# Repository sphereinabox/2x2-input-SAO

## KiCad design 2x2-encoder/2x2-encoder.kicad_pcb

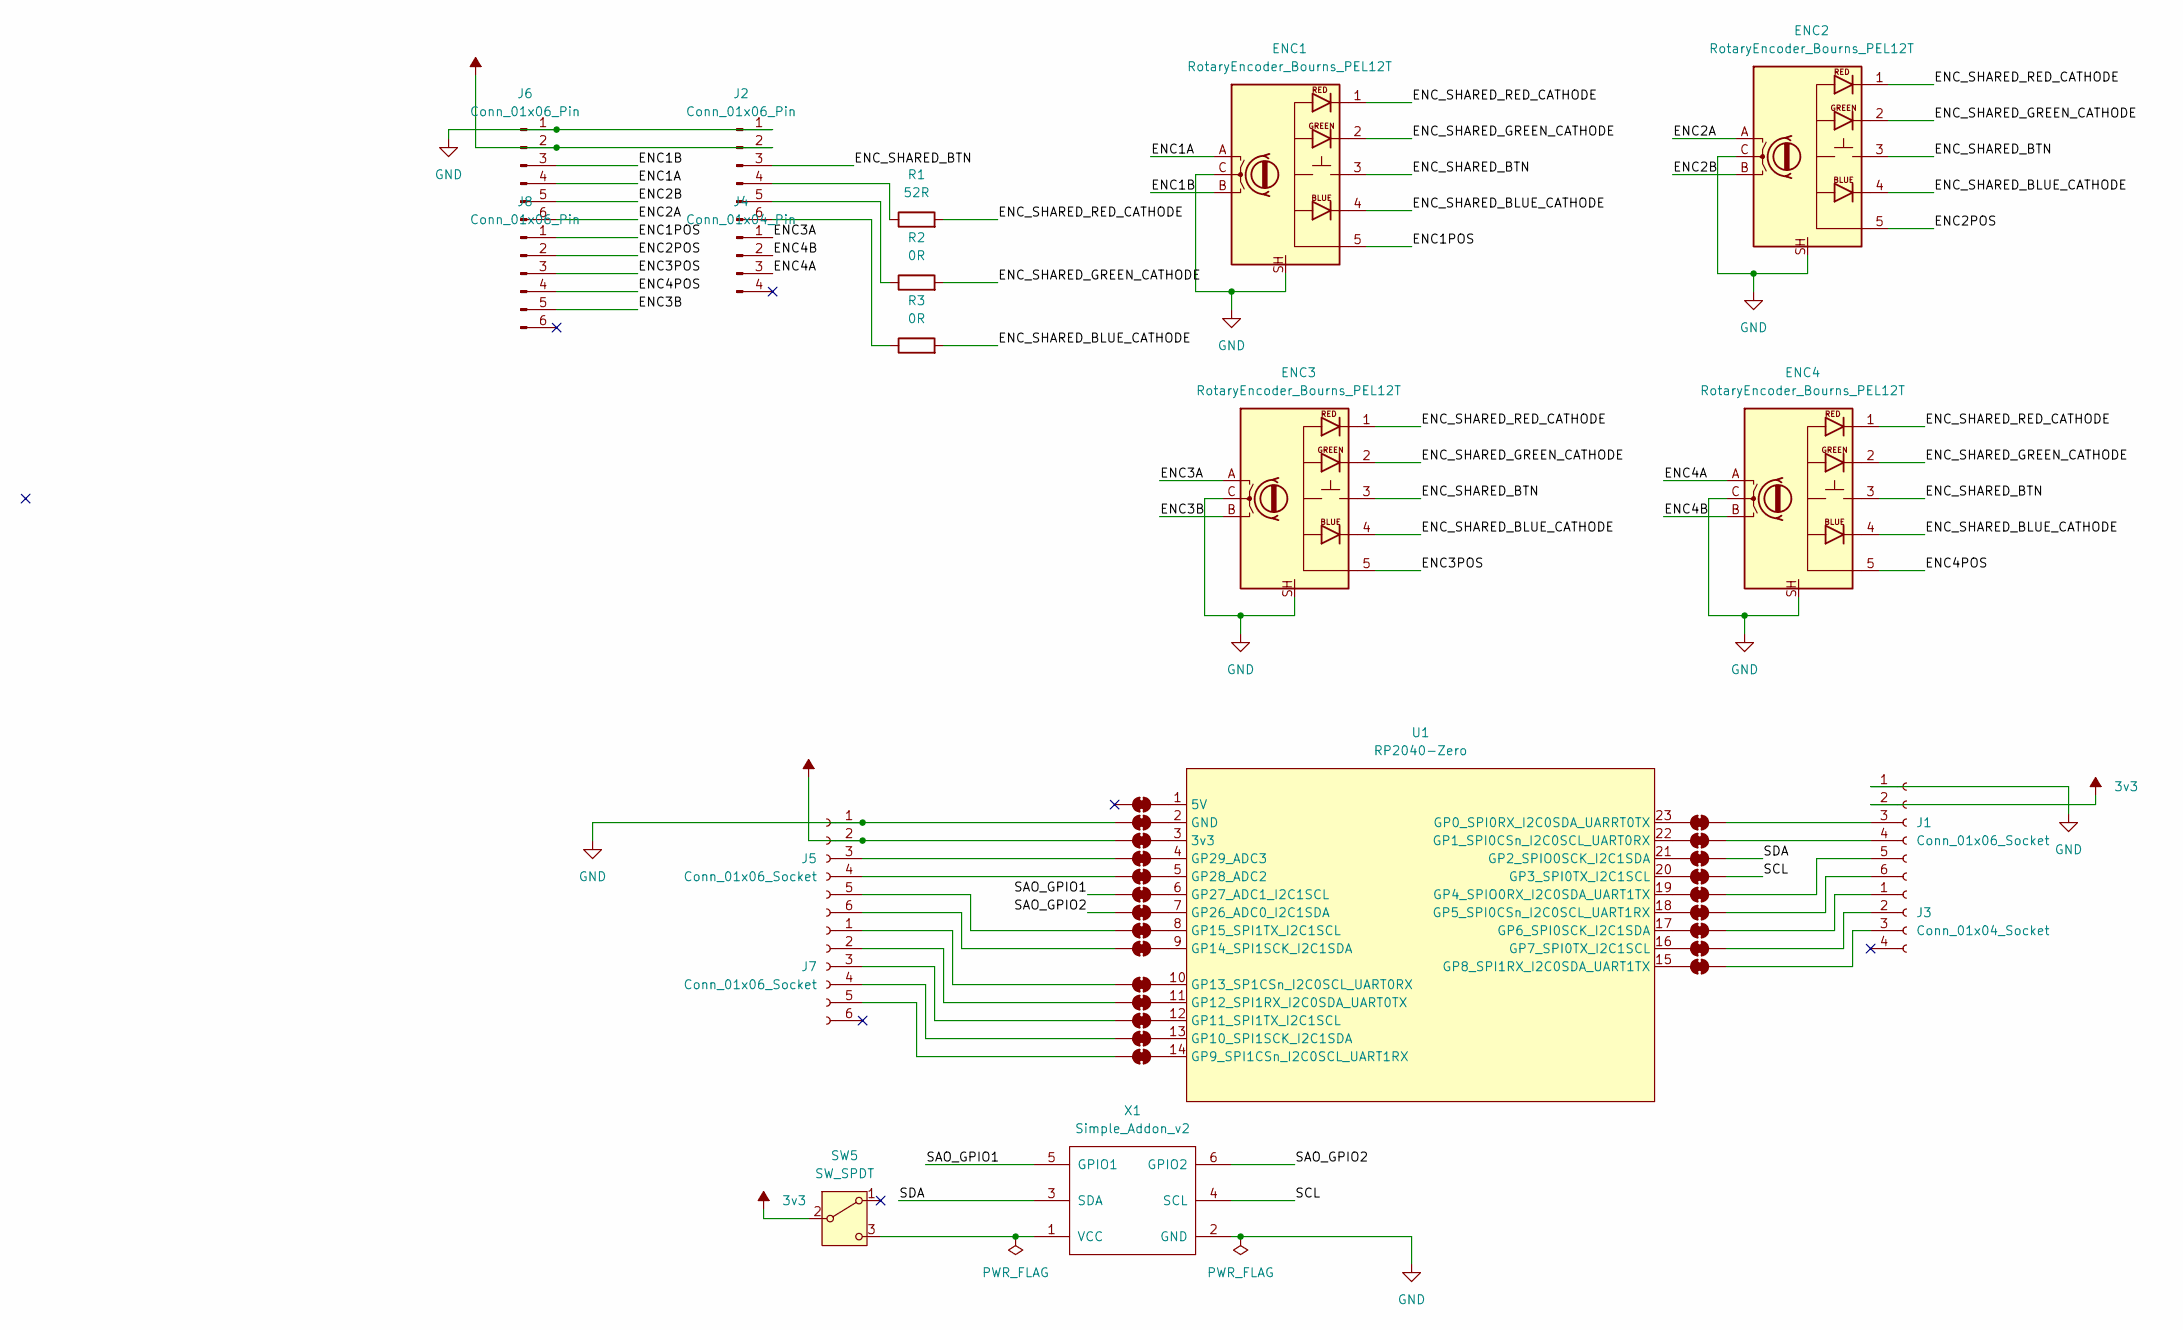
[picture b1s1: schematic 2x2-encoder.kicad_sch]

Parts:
ENC1, ENC2, ENC3, ENC4: RotaryEncoder_Bourns_PEL12T; RotaryEncoder_Bourns_Vertical_PEL12T-4x25S-Sxxxx
J1, J5, J7: Conn_01x06_Socket; PinSocket_1x06_P2.54mm_Vertical
J2, J6, J8: Conn_01x06_Pin; PinHeader_1x06_P2.54mm_Vertical
J3: Conn_01x04_Socket; PinSocket_1x04_P2.54mm_Vertical
J4: Conn_01x04_Pin; PinHeader_1x04_P2.54mm_Vertical
JP1, JP2, JP3, JP4, JP5, JP6, JP7, JP8, JP9, JP10, JP11, JP12, JP13, JP14, JP15, JP16, JP17, JP18, JP19, JP20, JP21, JP22, JP23: SolderJumper_2_Bridged; SolderJumper-2_P1.3mm_Bridged2Bar_Pad1.0x1.5mm
R1: 52R; R_0603_1608Metric_Pad0.98x0.95mm_HandSolder
R2, R3: 0R; R_0603_1608Metric_Pad0.98x0.95mm_HandSolder
SW5: SW_SPDT; SW_SPDT_PCM12
U1: RP2040-Zero; RP2040-Zero-PinHeaders
X1: Simple_Addon_v2; Simple_Addon_v2-SAO-2x3

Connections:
3v3: J1.2, J2.2, J5.2, J6.2, JP3.1 (A), SW5.2 (B)
/ENC1A: ENC1.A, J6.4
/ENC1B: ENC1.B, J6.3
/ENC1POS: ENC1.5, J8.1
/ENC2A: ENC2.A, J6.6
/ENC2B: ENC2.B, J6.5
/ENC2POS: ENC2.5, J8.2
/ENC3A: ENC3.A, J4.1
/ENC3B: ENC3.B, J8.5
/ENC3POS: ENC3.5, J8.3
/ENC4A: ENC4.A, J4.3
/ENC4B: ENC4.B, J4.2
/ENC4POS: ENC4.5, J8.4
/ENC_SHARED_BLUE_CATHODE: ENC1.4, ENC2.4, ENC3.4, ENC4.4, R3.2
/ENC_SHARED_BTN: ENC1.3, ENC2.3, ENC3.3, ENC4.3, J2.3
/ENC_SHARED_GREEN_CATHODE: ENC1.2, ENC2.2, ENC3.2, ENC4.2, R2.2
/ENC_SHARED_RED_CATHODE: ENC1.1, ENC2.1, ENC3.1, ENC4.1, R1.2
/SAO_GPIO1: JP6.1 (A), X1.5 (GPIO1)
/SAO_GPIO2: JP7.1 (A), X1.6 (GPIO2)
/SCL: JP18.2 (B), X1.4 (SCL)
/SDA: JP17.2 (B), X1.3 (SDA)
GND: ENC1.C, ENC1.SH, ENC2.C, ENC2.SH, ENC3.C, ENC3.SH, ENC4.C, ENC4.SH, J1.1, J2.1, J5.1, J6.1, JP2.1 (A), X1.2 (GND)
unnamed: J1.3, JP15.2 (B)
unnamed: J1.4, JP16.2 (B)
unnamed: J1.5, JP19.2 (B)
unnamed: J1.6, JP20.2 (B)
unnamed: J2.4, R1.1
unnamed: J2.5, R2.1
unnamed: J2.6, R3.1
unnamed: J3.1, JP21.2 (B)
unnamed: J3.2, JP22.2 (B)
unnamed: J3.3, JP23.2 (B)
unnamed: J5.3, JP4.1 (A)
unnamed: J5.4, JP5.1 (A)
unnamed: J5.5, JP8.1 (A)
unnamed: J5.6, JP9.1 (A)
unnamed: J7.1, JP10.1 (A)
unnamed: J7.2, JP11.1 (A)
unnamed: J7.3, JP12.1 (A)
unnamed: J7.4, JP13.1 (A)
unnamed: J7.5, JP14.1 (A)
unnamed: JP1.2 (B), U1.1 (5V)
unnamed: JP2.2 (B), U1.2 (GND)
unnamed: JP3.2 (B), U1.3 (3v3)
unnamed: JP4.2 (B), U1.4 (GP29_ADC3)
unnamed: JP5.2 (B), U1.5 (GP28_ADC2)
unnamed: JP6.2 (B), U1.6 (GP27_ADC1_I2C1SCL)
unnamed: JP7.2 (B), U1.7 (GP26_ADC0_I2C1SDA)
unnamed: JP8.2 (B), U1.8 (GP15_SPI1TX_I2C1SCL)
unnamed: JP9.2 (B), U1.9 (GP14_SPI1SCK_I2C1SDA)
unnamed: JP10.2 (B), U1.10 (GP13_SP1CSn_I2C0SCL_UART0RX)
unnamed: JP11.2 (B), U1.11 (GP12_SPI1RX_I2C0SDA_UART0TX)
unnamed: JP12.2 (B), U1.12 (GP11_SPI1TX_I2C1SCL)
unnamed: JP13.2 (B), U1.13 (GP10_SPI1SCK_I2C1SDA)
unnamed: JP14.2 (B), U1.14 (GP9_SPI1CSn_I2C0SCL_UART1RX)
unnamed: JP15.1 (A), U1.23 (GP0_SPI0RX_I2C0SDA_UARRT0TX)
unnamed: JP16.1 (A), U1.22 (GP1_SPI0CSn_I2C0SCL_UART0RX)
unnamed: JP17.1 (A), U1.21 (GP2_SPIO0SCK_I2C1SDA)
unnamed: JP18.1 (A), U1.20 (GP3_SPI0TX_I2C1SCL)
unnamed: JP19.1 (A), U1.19 (GP4_SPIO0RX_I2C0SDA_UART1TX)
unnamed: JP20.1 (A), U1.18 (GP5_SPI0CSn_I2C0SCL_UART1RX)
unnamed: JP21.1 (A), U1.17 (GP6_SPI0SCK_I2C1SDA)
unnamed: JP22.1 (A), U1.16 (GP7_SPI0TX_I2C1SCL)
unnamed: JP23.1 (A), U1.15 (GP8_SPI1RX_I2C0SDA_UART1TX)
unnamed: SW5.3 (C), X1.1 (VCC)

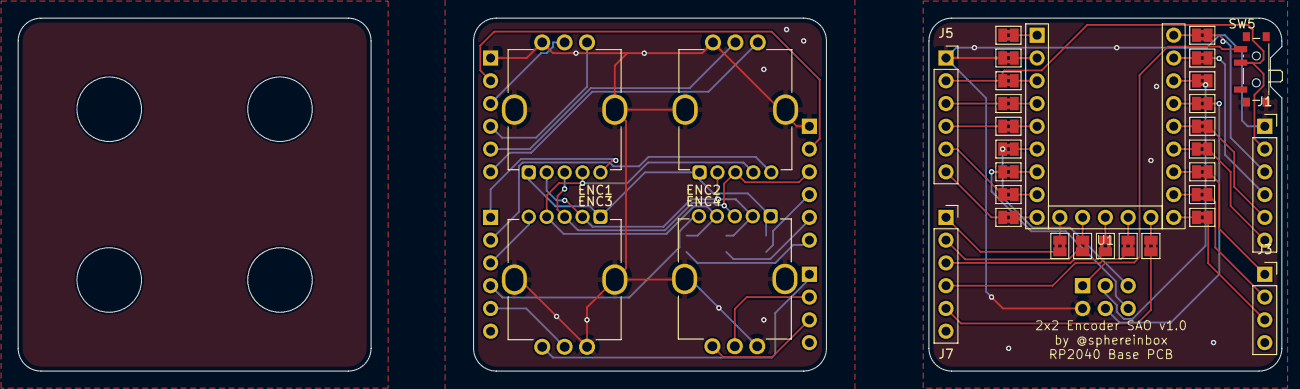
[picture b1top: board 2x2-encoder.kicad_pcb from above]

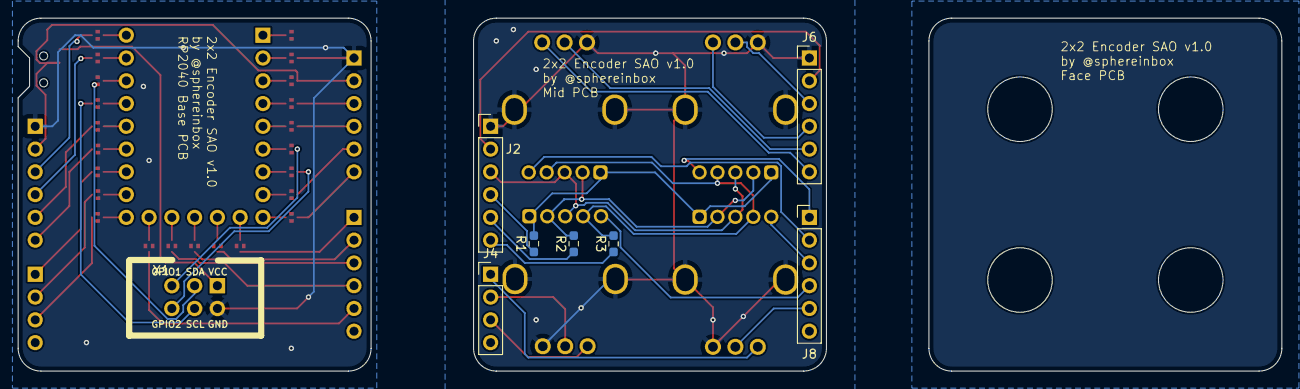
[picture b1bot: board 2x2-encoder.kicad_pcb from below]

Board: 2 copper layers, 141.0 x 39.4 mm, 44 parts (7 on the bottom side), 65 nets.

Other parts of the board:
REF_BOTTOM: Board
REF_MIDDLE: Board
REF_TOP: Board

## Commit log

2024-10-20 Initial Commit
    v1.0
2024-10-20 Changes for production export with kikit
2024-10-22 Add license
